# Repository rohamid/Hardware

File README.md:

# PCB-Files
This is my repository for all PCB project i have been working. Please note that i used EAGLE and KiCAD for every project

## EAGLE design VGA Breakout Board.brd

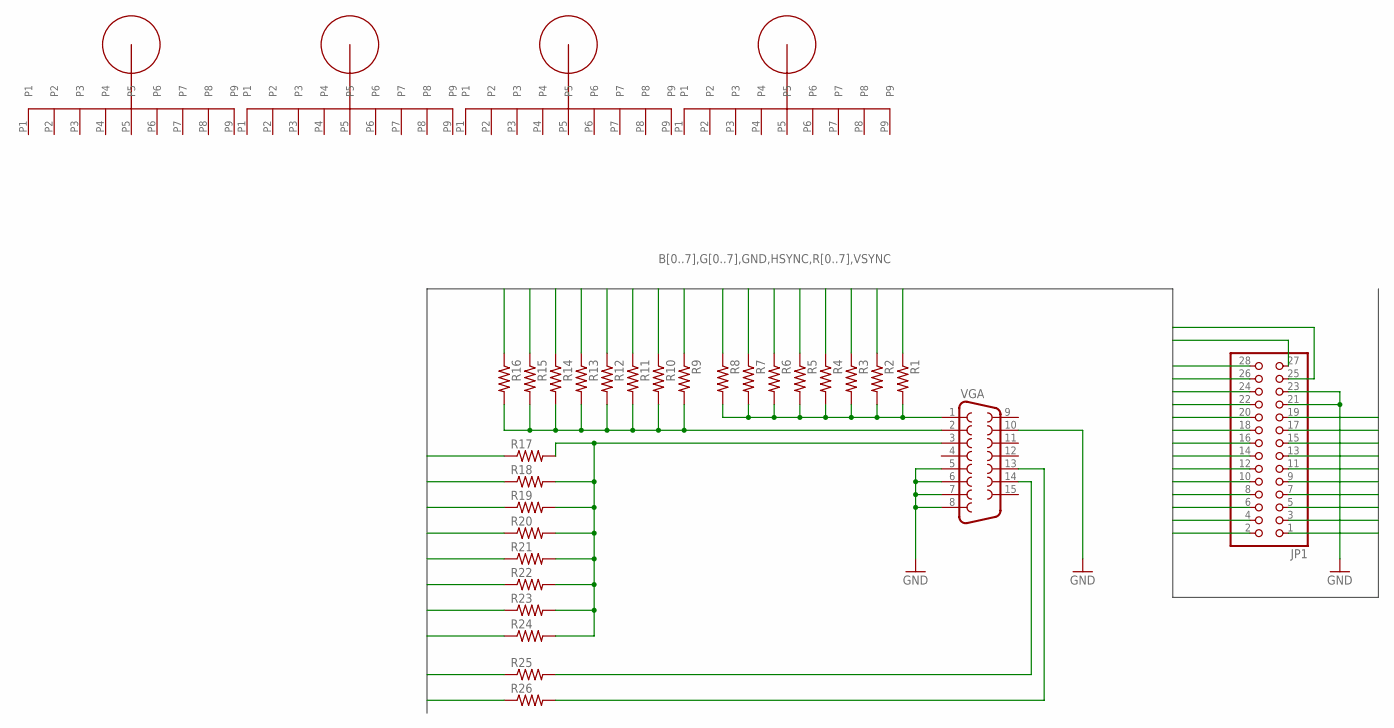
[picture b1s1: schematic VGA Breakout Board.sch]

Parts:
JP1: PINHD-2X14; 2X14
R1, R2, R3, R4, R5, R6, R7, R8, R9, R10, R11, R12, R13, R14, R15, R16, R17, R18, R19, R20, R21, R22, R23, R24, R25, R26: R-US_0207/10; 0207/10
U$1, U$2, U$3, U$4: STANDOFF
VGA: F15HDH; HDF15H

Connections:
B0: JP1.18, R17.1
B1: JP1.20, R18.1
B2: JP1.22, R19.1
B3: JP1.24, R20.1
B4: JP1.26, R21.1
B5: JP1.28, R22.1
B6: JP1.27, R23.1
B7: JP1.25, R24.1
G0: JP1.1, R9.1
G1: JP1.3, R10.1
G2: JP1.5, R11.1
G3: JP1.7, R12.1
G4: JP1.9, R13.1
G5: JP1.11, R14.1
G6: JP1.13, R15.1
G7: JP1.15, R16.1
GND: JP1.21, JP1.23, VGA.5, VGA.6, VGA.7, VGA.8, VGA.10
HSYNC: JP1.17, R26.1
unnamed: R1.2, R2.2, R3.2, R4.2, R5.2, R6.2, R7.2, R8.2, VGA.1
unnamed: R9.2, R10.2, R11.2, R12.2, R13.2, R14.2, R15.2, R16.2, VGA.2
unnamed: R17.2, R18.2, R19.2, R20.2, R21.2, R22.2, R23.2, R24.2, VGA.3
unnamed: R25.2, VGA.14
unnamed: R26.2, VGA.13
R0: JP1.16, R1.1
R1: JP1.14, R2.1
R2: JP1.12, R3.1
R3: JP1.10, R4.1
R4: JP1.8, R5.1
R5: JP1.6, R6.1
R6: JP1.4, R7.1
R7: JP1.2, R8.1
VSYNC: JP1.19, R25.1

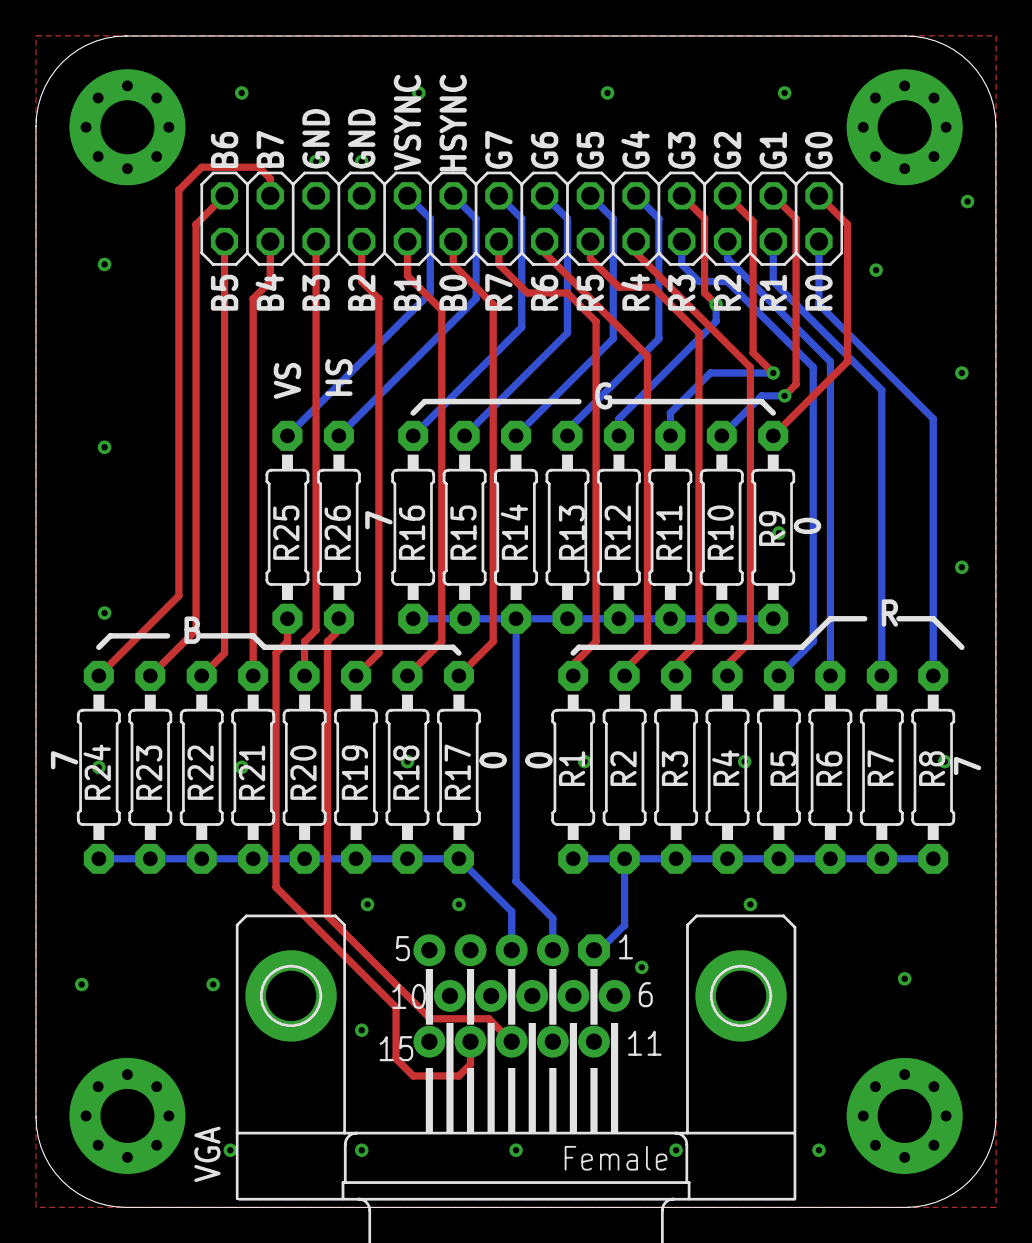
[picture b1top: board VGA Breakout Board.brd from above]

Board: 2 copper layers, 53.3 x 65.1 mm, 32 parts (0 on the bottom side), 32 nets.
